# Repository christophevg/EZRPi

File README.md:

# EZRPi
Raspberry Pi HAT with a Silicon Labs EZR32 Sub-GHz MCU  
Christophe VG (<contact@christophe.vg>)  
[http://christophe.vg/embedded/EZRPi](http://christophe.vg/embedded/EZRPi)

## Introduction

Using the EZRPi HAT one can give access to sub-GHz network protocols to a Raspberry Pi. An example of such protocol is Dash7. Dash7 is a specification for an ultra low power network stack, operating within the sub-GHz spectrum. The [Dash7 Open Source Stack (OSS-7)](https://github.com/MOSAIC-LoPoW/dash7-ap-open-source-stack) can be flashed onto the EZR to turn it into a modem, accessible from the Raspberry Pi. On the Pi, one then could talk to this modem using [pyd7a](https://github.com/MOSAIC-LoPoW/pyd7a) a collection of Python modules, supporting the DASH7 Alliance Protocol in general, and OSS-7 in particular..

This repository contains all design and implementation source files of this generic sub-GHz Raspberry Pi HAT.

## Version 1

On Thursday March 30, I was able to assemble the first EZRPi:

The design includes a standard 868MHz setup of the EZR32 and two LEDs for minimal debugging/feedback.

The board is a 2-layer PCB based on the official Raspberry Pi HAT board specification.

## Software

In the `src/` folder a first small test application is included: [`blink`](src/blink). It requires the `Gecko SDK`, which is included as a submodule in the `lib/` folder.

### OSS-7 Support

As of [Friday March 21](https://github.com/MOSAIC-LoPoW/dash7-ap-open-source-stack/pull/51), the [Dash7 Open Source Stack](https://github.com/MOSAIC-LoPoW/dash7-ap-open-source-stack) now also includes a platform definition for the EZRPi. This makes it super-easy to add Dash7 support to the Raspberry Pi:

```bash
$ git clone https://github.com/MOSAIC-LoPoW/dash7-ap-open-source-stack
Cloning into 'dash7-ap-open-source-stack'...
remote: Counting objects: 39483, done.
remote: Compressing objects: 100% (291/291), done.
remote: Total 39483 (delta 164), reused 0 (delta 0), pack-reused 39191
Receiving objects: 100% (39483/39483), 71.42 MiB | 8.46 MiB/s, done.
Resolving deltas: 100% (27893/27893), done.

$ cd dash7-ap-open-source-stack

$ mkdir build

$ cd build

$ cmake ../stack/ \
        -DCMAKE_TOOLCHAIN_FILE=../stack/cmake/toolchains/gcc-arm-embedded.cmake \
        -DPLATFORM=EZRPi \
        -DAPP_SENSOR_PUSH=on \
        -DFRAMEWORK_LOG_ENABLED=yes \
        -DFRAMEWORK_DEBUG_ASSERT_MINIMAL=y
-- Cross-compiling using gcc-arm-embedded toolchain
-- Cross-compiling using gcc-arm-embedded toolchain
-- The C compiler identification is GNU 4.9.3
-- The CXX compiler identification is GNU 4.9.3
-- Detecting C compiler ABI info
-- Detecting C compiler ABI info - failed
-- Detecting C compile features
-- Detecting C compile features - failed
-- Detecting CXX compiler ABI info
-- Detecting CXX compiler ABI info - failed
-- Detecting CXX compile features
-- Detecting CXX compile features - failed
-- detected supported platforms: EFM32GG_STK3700 EFM32HG_STK3400 EZR32LG_Octa EZR32LG_USB01 EZR32LG_WSTK6200A EZRPi OCTA_Gateway stm32f4_discovery
-- selected platform: EZRPi
-- The ASM compiler identification is GNU
-- Found assembler: /usr/local/bin/arm-none-eabi-gcc
-- Added chip ezr32lg
-- Added chip si4460
-- Configuring done
-- Generating done
-- Build files have been written to: /Users/xtof/dash7-ap-open-source-stack/build

$ make
Scanning dependencies of target CHIP_SI4460
[  1%] Building C object framework/hal/platforms/platform/chips/si4460/CMakeFiles/CHIP_SI4460.dir/si4460.c.obj
...
[ 98%] Building C object apps/sensor_push/CMakeFiles/sensor_push.elf.dir/version.c.obj
[100%] Linking C executable sensor_push.elf
[100%] Built target sensor_push.elf

$ make flash-sensor_push
[ 14%] Built target d7ap
[ 22%] Built target CHIP_SI4460
...
Downloading file [sensor_push.bin]...
Comparing flash   [100%] Done.
Erasing flash     [100%] Done.
Programming flash [100%] Done.
Verifying flash   [100%] Done.
J-Link: Flash download: Flash programming performed for 3 ranges (77824 bytes)
J-Link: Flash download: Total time needed: 1.960s (Prepare: 0.052s, Compare: 0.062s, Erase: 0.933s, Program: 0.896s, Verify: 0.008s, Restore: 0.007s)
O.K.

Loading binary file sensor_push.bin
Reading 81476 bytes data from target memory @ 0x00000000.
Verify successful.

Reset delay: 0 ms
Reset type NORMAL: Resets core & peripherals via SYSRESETREQ & VECTRESET bit.

Script processing completed.

[100%] Built target flash-sensor_push

```

The EZRPi has been tested against the EZR32LG_USB01 and bi-directional communication was achieved.

## Thanks

Although merely a software-implementation option, many thanks go out to the Dash7 Alliance and the OSS-7 team for creating the Dash7 network stack specification in all openness. Special thanks go out to Maarten W. for his support in making this project a reality.

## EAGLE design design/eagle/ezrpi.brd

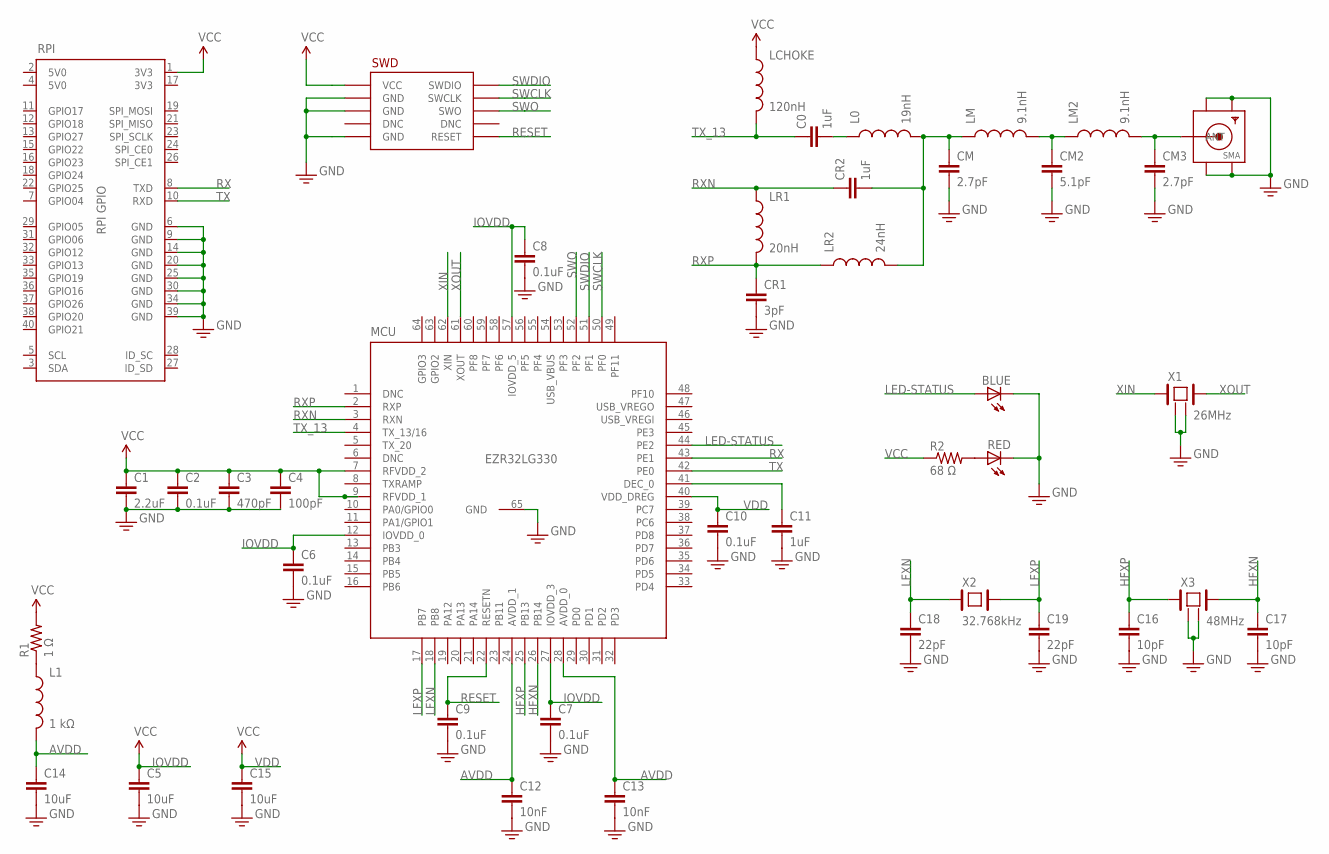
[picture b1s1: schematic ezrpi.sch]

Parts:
BLUE: LEDCHIPLED_0805; CHIPLED_0805
C0, C11: 1uF; 0805
C1: 2.2uF; 0805
C2, C6, C7, C8, C9, C10: 0.1uF; 0805
C3: 470pF; 0805
C4: 100pF; 0805
C5, C14, C15: 10uF; 0805
C12, C13: 10nF; 0805
C16, C17: 10pF; 0805
C18, C19: 22pF; 0805
CM, CM3: 2.7pF; 0805
CM2: 5.1pF; 0805
CR1: 3pF; 0805
CR2: 1uF; 0805
L0: 19nH; C0402
L1: 1 kΩ; 0805
LCHOKE: 120nH; 0805
LM, LM2: 9.1nH; 0805
LR1: 20nH; 0805
LR2: 24nH; 0805
MCU: EZR32LG330; QFN64G-0.5-9X9MM
R1: 1 Ω; 0805
R2: 68 Ω; 0805
RED: LEDCHIPLED_0805; CHIPLED_0805
RPI: RPI3_HAT; RASPI_BOARD_B+HAT_DF_CF
SMA: SMACONNECTOR; SMA90_DIP
SWD: FTSH2X5; HEADER2X5
X1: 26MHz; ABM8
X2: 32.768kHz; MS3V-T1R
X3: 48MHz; ABM11

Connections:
3V3: RPI.17 (3V3)
5V0: RPI.2 (5V0), RPI.4 (5V0)
AVDD: C12.1, C13.1, C14.1, L1.2, MCU.24 (AVDD_1), MCU.28 (AVDD_0)
GND: BLUE.C, C1.2, C2.2, C3.2, C4.2, C5.2, C6.2, C7.2, C8.2, C9.2, C10.2, C11.2, C12.2, C13.2, C14.2, C15.2, C16.2, C17.2, C18.2, C19.2, CM.2, CM2.2, CM3.2, CR1.2, MCU.65 (GND), RED.C, RPI.6 (GND), RPI.9 (GND), RPI.14 (GND), RPI.20 (GND), RPI.25 (GND), RPI.30 (GND), RPI.34 (GND), RPI.39 (GND), SMA.GND1, SMA.GND2, SMA.GND3, SMA.GND4, SWD.P$3 (GND), SWD.P$5 (GND), SWD.P$9 (GND), X1.2 (GND), X1.4 (GND), X3.2 (GND), X3.4 (GND)
HFXN: C17.1, MCU.26 (PB14), X3.3
HFXP: C16.1, MCU.25 (PB13), X3.1
IOVDD: C5.1, C6.1, C7.1, C8.1, MCU.12 (IOVDD_0), MCU.27 (IOVDD_3), MCU.57 (IOVDD_5)
LED-STATUS: BLUE.A, MCU.44 (PE2)
LFXN: C18.1, MCU.18 (PB8), X2.1
LFXP: C19.1, MCU.17 (PB7), X2.2
unnamed: CM3.1, LM2.2, SMA.ANTENNA (ANT)
unnamed: C11.1, MCU.41 (DEC_0)
unnamed: CM2.1, LM.2, LM2.1
unnamed: L1.1, R1.1
unnamed: C0.2, L0.1
unnamed: CM.1, CR2.2, L0.2, LM.1, LR2.2
unnamed: R2.2, RED.A
RESET: C9.1, MCU.22 (RESETN), SWD.P$10 (RESET)
RX: MCU.43 (PE1), RPI.8 (TXD)
RXN: CR2.1, LR1.1, MCU.3 (RXN)
RXP: CR1.1, LR1.2, LR2.1, MCU.2 (RXP)
SWCLK: MCU.50 (PF0), SWD.P$4 (SWCLK)
SWDIO: MCU.51 (PF1), SWD.P$2 (SWDIO)
SWO: MCU.52 (PF2), SWD.P$6 (SWO)
TX: MCU.42 (PE0), RPI.10 (RXD)
TX_13: C0.1, LCHOKE.2, MCU.4 (TX_13/16)
VCC: C1.1, C2.1, C3.1, C4.1, LCHOKE.1, MCU.7 (RFVDD_2), MCU.9 (RFVDD_1), R1.2, R2.1, RPI.1 (3V3), SWD.P$1 (VCC)
VDD: C10.1, C15.1, MCU.40 (VDD_DREG)
XIN: MCU.62 (XIN), X1.1
XOUT: MCU.61 (XOUT), X1.3

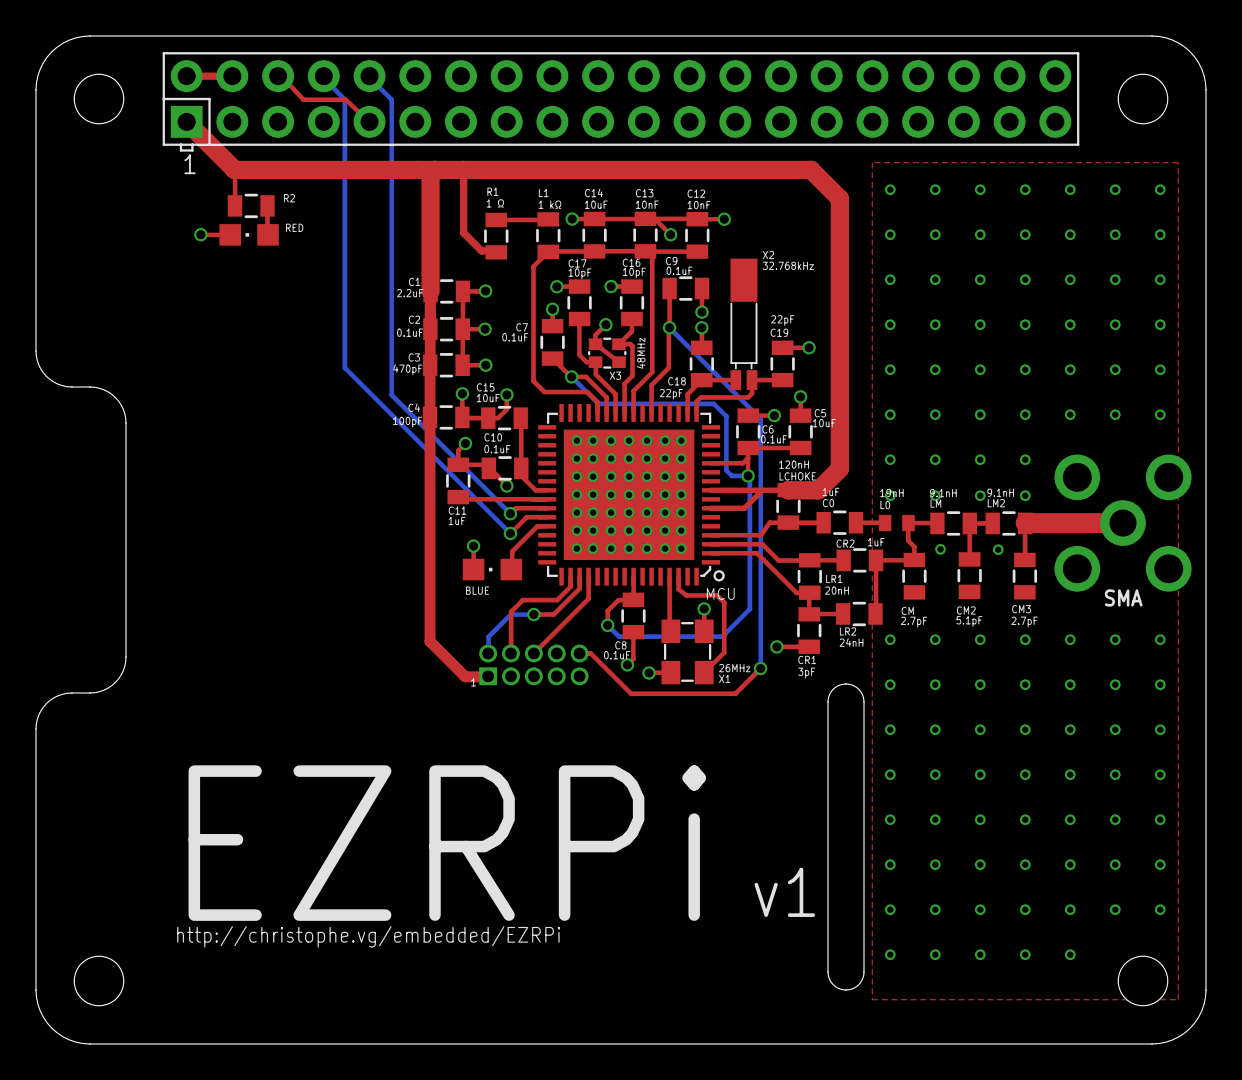
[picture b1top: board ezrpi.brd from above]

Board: 2 copper layers, 65.0 x 56.0 mm, 43 parts (0 on the bottom side), 29 nets.

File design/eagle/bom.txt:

Partlist exported from /Users/xtof/Workspace/EZRPi/design/eagle/ezrpi.sch at 09/03/2017 17:16

Qty Value      Device           Package                 Parts                   Description   
1              SMACONNECTOR     SMA90_DIP               SMA                     SMA Connector 
6   0.1uF      CAP0805          0805                    C2, C6, C7, C8, C9, C10 Capacitor     
1   1 kΩ       INDUCTOR0805     0805                    L1                      Inductors     
1   1 Ω        RESISTOR0805-RES 0805                    R1                      Resistor      
1   100pF      CAP0805          0805                    C4                      Capacitor     
2   10nF       CAP0805          0805                    C12, C13                Capacitor     
2   10pF       CAP0805          0805                    C16, C17                Capacitor     
3   10uF       CAP0805          0805                    C5, C14, C15            Capacitor     
1   120nH      INDUCTOR0805     0805                    LCHOKE                  Inductors     
1   19nH       INDUCTOR0402     C0402                   L0                      Inductors     
3   1uF        CAP0805          0805                    C0, C11, CR2            Capacitor     
1   2.2uF      CAP0805          0805                    C1                      Capacitor     
2   2.7pF      CAP0805          0805                    CM, CM3                 Capacitor     
1   20nH       INDUCTOR0805     0805                    LR1                     Inductors     
2   22pF       CAP0805          0805                    C18, C19                Capacitor     
1   24nH       INDUCTOR0805     0805                    LR2                     Inductors     
1   26MHz      ABM8             ABM8                    X1                                    
1   32.768kHz  MS3V-T1R         MS3V-T1R                X2                                    
1   3pF        CAP0805          0805                    CR1                     Capacitor     
1   470pF      CAP0805          0805                    C3                      Capacitor     
1   48MHz      ABM11            ABM11                   X3                                    
1   5.1pF      CAP0805          0805                    CM2                     Capacitor     
2   9.1nH      INDUCTOR0805     0805                    LM, LM2                 Inductors     
1   EZR32LG330 EZR32LG330       QFN64G-0.5-9X9MM        MCU                                   
1   FTSH2X5    FTSH2X5          HEADER2X5               SWD                                   
1   RPI3_HAT   RPI3_HAT         RASPI_BOARD_B+HAT_DF_CF RPI

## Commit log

2016-12-06 init repo
2016-12-06 ignoring temp eagle files
2016-12-06 added initial setup of MCU + decoupling
2016-12-06 ignoring MacOS caches
2016-12-06 added documentation on HATs and GPIO header
2016-12-07 ignoring lock files
2016-12-07 added EZR reference documentation
2016-12-08 redesigned to match AN0016 + added JTAG (6pins)
2016-12-08 cleaned up project file
2016-12-08 added crystals
2017-02-15 rebranded project to generic EZRPi sub-GHz HAT
2017-03-08 added datasheets for crystals
2017-03-08 added app note on pa matching
2017-03-08 completed schematic, started work on board design
2017-03-09 completed schematic and first board layout
2017-03-09 fixed some design rules violations
2017-03-09 fixed incorrect pin connection on IOVDD_0
2017-03-09 unified cap value 100nF = 0.1uF
2017-03-09 added top ground plane, fixed silk & naming
2017-03-09 moved tValues to tNames (EC)
2017-03-09 added some green-(silk-)space filling ;-)
2017-03-09 added url
2017-03-09 added LEDs, improved traces, 50 Ω line, added vias
2017-03-09 added more fence vias
2017-03-09 added v1 visuals to README
2017-03-10 added EC visualisation
2017-03-10 added back-link to information webpage
2017-03-10 added “thanks” section to README
2017-03-10 added license information
2017-03-29 setup lib/ dir with notice on Gecko_SDK
2017-03-29 added draft “blink” example using emlib & co
2017-03-30 removed (mostly redundant) selection of programmer
2017-03-30 setup for correct EZR(Pi)
2017-03-30 ignoring flash script
2017-03-30 added info on first sign of life of the EZRPi v1
2017-03-30 added reference to start of software
2017-03-31 added info on Dash7 platform definition
2017-03-31 introduced Gek SDK as submodule
2017-03-31 added README to blink + some build clean up
2017-03-31 reduced image sizes
2017-03-31 fixed formatting of link
2017-05-02 update BOM
